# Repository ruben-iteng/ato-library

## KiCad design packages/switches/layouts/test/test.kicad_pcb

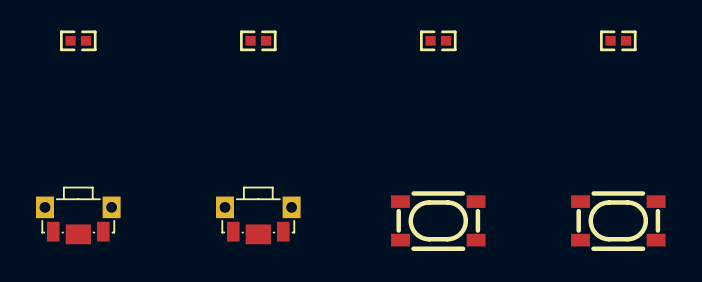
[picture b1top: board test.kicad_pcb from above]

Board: 2 copper layers, 8 parts (0 on the bottom side), 6 nets, no tracks yet.

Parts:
R1, R2, R3, R4: 10kΩ ±1% 62.5mW; R0402
U1, U3: KEY-SMD_SKTDLDE010
U2, U4: KEY-SMD_4P-L4.2-W3.2-P2.20-LS4.6

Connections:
gnd: U4.3, U4.4
hv: U2.3, U2.4
line: R4.1, U4.1, U4.2
line-1: R3.1, U3.1
line-2: R2.1, U2.1, U2.2
line-3: R1.1, U1.1

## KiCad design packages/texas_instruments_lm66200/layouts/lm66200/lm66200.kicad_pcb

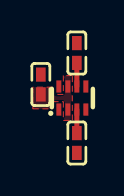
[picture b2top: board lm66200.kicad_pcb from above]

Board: 2 copper layers, 4 parts (0 on the bottom side), 4 nets.

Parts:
C1, C2, C3: 100nF ±10% 16V X7R; C0402
U1: SOT-583-8_L2.1-W1.2-P0.50-LS1.6-BL

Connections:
VOUT: C3.1, U1.2, U1.7
gnd: C1.2, C2.2, C3.2, U1.1, U1.5
hv: C1.1, U1.3
hv-1: C2.1, U1.6

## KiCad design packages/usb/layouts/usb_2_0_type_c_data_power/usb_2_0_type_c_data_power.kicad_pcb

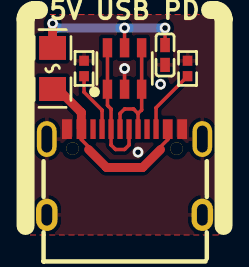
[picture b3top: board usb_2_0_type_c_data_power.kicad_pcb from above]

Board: 2 copper layers, 6 parts (0 on the bottom side), 7 nets.

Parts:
C1: 100nF ±10% 16V X7R; C0402-b3ef17
R1, R2: 5.1kΩ ±1% 62.5mW; R0402-56259e
U1: SOT-23-6_L2.9-W1.6-P0.95-LS2.8-BL-d2c740
U2: F0805-d5954a
USB1: USB-C-SMD_TYPE-C-6PIN-2MD-073-1d78f0

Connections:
CC1: R1.1, USB1.4
CC2: R2.1, USB1.10
VBUS: U2.1, USB1.2, USB1.11
gnd: C1.2, R1.2, R2.2, U1.2, USB1.1, USB1.12, USB1.13, USB1.14
hv: C1.1, U1.5, U2.2
line: U1.1, U1.6, USB1.5, USB1.7
line-1: U1.3, U1.4, USB1.6, USB1.8

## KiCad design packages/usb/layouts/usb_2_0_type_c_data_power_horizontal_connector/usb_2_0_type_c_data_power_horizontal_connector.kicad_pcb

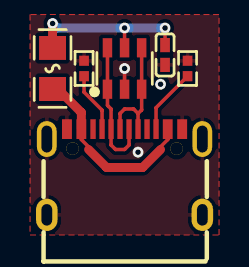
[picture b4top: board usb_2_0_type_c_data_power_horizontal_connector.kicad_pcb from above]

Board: 2 copper layers, 6 parts (0 on the bottom side), 7 nets.

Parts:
C1: 100nF ±10% 16V X7R; C0402
F1: F0805
R1, R2: 5.1kΩ ±1% 62.5mW; R0402
U1: SOT-23-6_L2.9-W1.6-P0.95-LS2.8-BL
X1: USB-C-SMD_TYPE-C-6PIN-2MD-073

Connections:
gnd: C1.2, R1.2, R2.2, U1.2, X1.1, X1.12, X1.13, X1.14
hv: F1.1, X1.2, X1.11
hv-1: C1.1, F1.2, U1.5
line: R1.1, X1.4
line-1: R2.1, X1.10
line-4: U1.1, U1.6, X1.5, X1.7
line-5: U1.3, U1.4, X1.6, X1.8

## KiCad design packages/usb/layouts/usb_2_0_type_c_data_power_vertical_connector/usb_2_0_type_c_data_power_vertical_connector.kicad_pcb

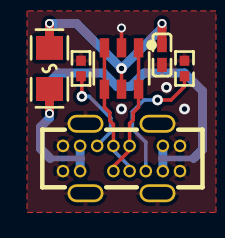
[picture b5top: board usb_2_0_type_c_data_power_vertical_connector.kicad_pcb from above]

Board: 2 copper layers, 6 parts (0 on the bottom side), 7 nets.

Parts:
C1: 100nF ±10% 16V X7R; C0402
F1: F0805
R1, R2: 5.1kΩ ±1% 62.5mW; R0402
U1: SOT-23-6_L2.9-W1.6-P0.95-LS2.8-BL
X1: USB-C-TH_TYPE-C-USB-14P

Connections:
gnd: C1.2, R1.2, R2.2, U1.2, X1.0, X1.1, X1.7, X1.8, X1.14
hv: F1.1, X1.2, X1.6, X1.9, X1.13
hv-1: C1.1, F1.2, U1.5
line: R1.1, X1.12
line-1: R2.1, X1.5
line-2: U1.1, U1.6, X1.3, X1.10
line-3: U1.3, U1.4, X1.4, X1.11

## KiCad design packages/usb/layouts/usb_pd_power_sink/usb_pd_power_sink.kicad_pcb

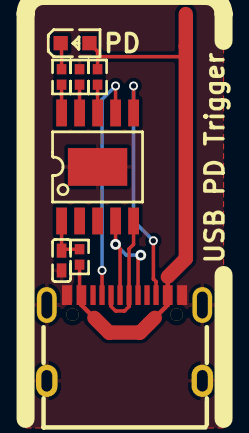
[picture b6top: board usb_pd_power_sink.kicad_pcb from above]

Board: 2 copper layers, 8 parts (0 on the bottom side), 11 nets.

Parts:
C1: 1µF ±10% 25V X5R; C0402-b3ef17
R1, R2, R4: 10kΩ ±1% 62.5mW; R0402-56259e
R3: 1kΩ ±1% 62.5mW; R0402-56259e
U1: ESSOP-10_L4.9-W3.9-P1.0-LS6.0-TL-EP-20a8ca
U2: LED0603-RD
USB1: USB-C-SMD_TYPE-C-6PIN-2MD-073-1d78f0

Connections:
DN2: U1.5, USB1.5, USB1.7
DP2: U1.4, USB1.6, USB1.8
anode: R2.1, R3.1, U2.2, USB1.2, USB1.11
cathode: R1.1, U2.1
gnd: C1.2, R4.2, U1.11, USB1.1, USB1.12, USB1.13, USB1.14
hv: C1.1, R3.2, U1.1
line: U1.6, USB1.10
line-1: U1.7, USB1.4
pd_trigger-gnd: R1.2, U1.10
pd_trigger-line: R4.1, U1.9
pd_trigger-line-1: R2.2, U1.8

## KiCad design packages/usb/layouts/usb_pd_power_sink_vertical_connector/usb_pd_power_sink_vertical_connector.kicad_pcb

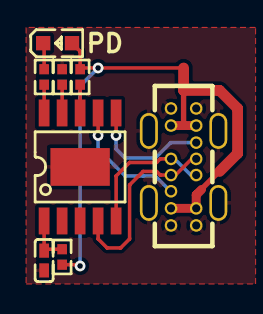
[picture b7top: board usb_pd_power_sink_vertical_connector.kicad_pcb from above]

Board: 2 copper layers, 8 parts (0 on the bottom side), 11 nets.

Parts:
C1: 1µF ±10% 25V X5R; C0402
LED1: LED0603-RD
R1, R2, R4: 10kΩ ±1% 62.5mW; R0402
R3: 1kΩ ±1% 62.5mW; R0402
U1: ESSOP-10_L4.9-W3.9-P1.0-LS6.0-TL-EP
X1: USB-C-TH_TYPE-C-USB-14P

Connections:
Dneg: U1.5, X1.3, X1.10
Dpos: U1.4, X1.4, X1.11
anode: LED1.2, R2.1, R3.1, X1.2, X1.6, X1.9, X1.13
cathode: LED1.1, R1.1
gnd: C1.2, R4.2, U1.11, X1.0, X1.1, X1.7, X1.8, X1.14
hv: C1.1, R3.2, U1.1
line: U1.7, X1.12
line-1: U1.6, X1.5
pd_trigger-gnd: R1.2, U1.10
pd_trigger-line: R4.1, U1.9
pd_trigger-line-1: R2.2, U1.8
